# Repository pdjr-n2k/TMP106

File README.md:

# TMP106 - NMEA 2000 temperature sensor module

This project provides a 
[hardware design](./hardware/)
and associated
[firmware](./firmware/)
for an NMEA 2000 six channel temperature sensor module.

There is also a
[user manual](./user/README.md)
for a device built using these two components.

**TMP106** is a specialisation of
[NOP100](https://www.github.com/preeve9534/NOP100).

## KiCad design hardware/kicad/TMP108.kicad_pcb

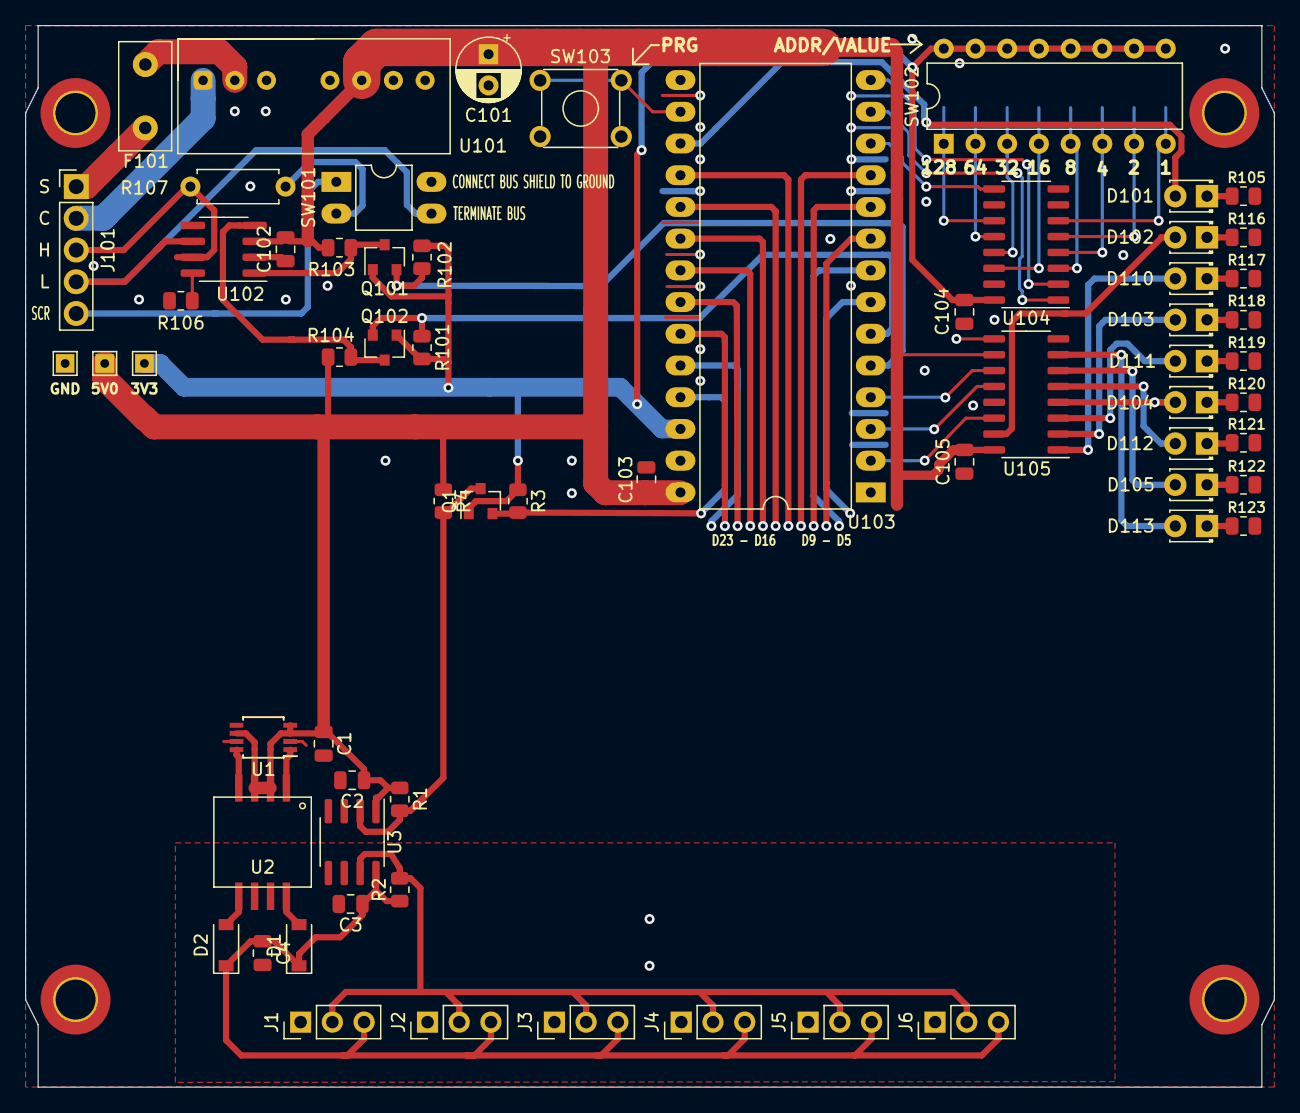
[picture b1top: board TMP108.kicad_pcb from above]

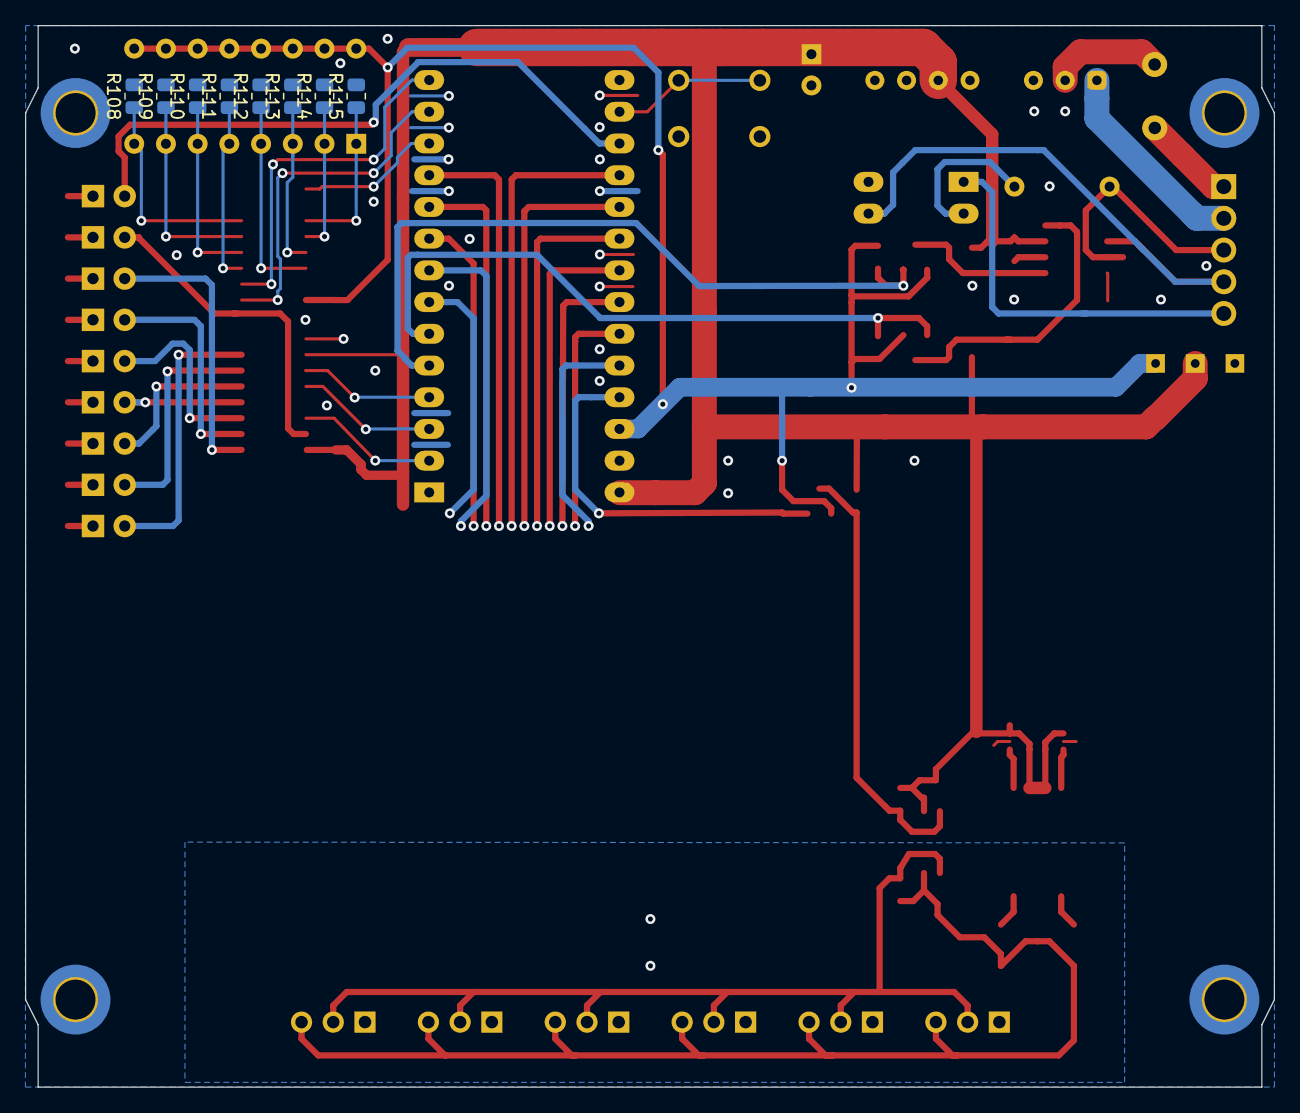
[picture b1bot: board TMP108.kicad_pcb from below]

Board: 2 copper layers, 100.0 x 85.0 mm, 71 parts (8 on the bottom side), 57 nets.

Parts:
C1, C3: 10uF; C_0805_2012Metric
C2, C4: 20nF; C_0805_2012Metric
C101: 100nF; CP_Radial_D5.0mm_P2.50mm
C102, C103, C104, C105: 100nF; C_0805_2012Metric
D1, D2: MBR0520LT; D_SOD-123
D101, D102, D103, D104, D105, D110, D111, D112, D113: LED; LED_D1.8mm_W3.3mm_H2.4mm
F101: 1A; Fuse_Littelfuse_395Series
J1, J2, J3, J4, J5, J6: Screw_Terminal_01x03; PinHeader_1x03_P2.54mm_Vertical
J101: CAN; PinHeader_1x05_P2.54mm_Vertical
Q1, Q101, Q102: BSS138; SOT-23
R1, R2: 1K; R_0805_2012Metric
R3, R4: 10K; R_0805_2012Metric
R101, R102, R103, R104: 10K 0.125W; R_0805_2012Metric
R105, R116, R117, R118, R119, R120, R121, R122, R123: 560R; R_0805_2012Metric
R106, R108, R109, R110, R111, R112, R113, R114, R115: 4K7 0.125W; R_0805_2012Metric
R107: 120R 0.5W; R_Axial_DIN0207_L6.3mm_D2.5mm_P7.62mm_Horizontal
SW101: BUS; DIP-4_W7.62mm_LongPads
SW102: ADDR/VALUE; DIP-16_W7.62mm
SW103: PRG; SW_TH_Tactile_Omron_B3F-10xx
TEST 5V0, TEST 5V0#2: TestPoint_THTPad_1.5x1.5mm_Drill0.7mm
U1: MAX845; TSSOP-8_3x3mm_P0.65mm
U2: TGM-050P3RL; TGM-010P3RL
U3: ISO1540; SOIC-8_3.9x4.9mm_P1.27mm
U101: TMR-2-2411; TMR_2411
U102: MCP2551-I-P; SOIC-8_3.9x4.9mm_P1.27mm
U103: Teensy_4.0; DIP-28_W15.24mm_LongPads
U104: 74HC165; SO-16_3.9x9.9mm_P1.27mm
U105: 74HCT595; SO-16_3.9x9.9mm_P1.27mm

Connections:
+3V3: C104.1, Q1.1, Q101.1, Q102.1, R3.1, R101.2, R102.2, SW102.9, SW102.10, SW102.11, SW102.12, SW102.13, SW102.14, SW102.15, SW102.16, TEST 5V0.1, U103.26, U104.16
+5V: C1.1, C2.1, C101.1, C102.1, C103.1, C105.1, R1.1, R4.1, R103.2, R104.2, TEST 5V0#2.1, U1.3, U1.4, U1.6, U2.2, U2.3, U3.1, U101.6, U102.3, U103.28, U105.10, U105.16
/CAN_RX: Q102.2, R101.1, U103.6
/CAN_TX: Q101.2, R102.1, U103.5
/D23: Q1.2, R3.2, U103.25
/PISO_CP: U103.14, U104.2
/PISO_PL: U103.13, U104.1
/PISO_Q7: U103.12, U104.9
/PRG: SW103.1, SW103.2, U103.16
/SIPO_CLOCK: U103.4, U105.11
/SIPO_DATA: U103.2, U105.14
/SIPO_LATCH: U103.3, U105.12
GND: C1.2, C2.2, C101.2, C102.2, C103.2, C104.2, C105.2, R105.2, R106.1, R108.2, R109.2, R110.2, R111.2, R112.2, R113.2, R114.2, R115.2, R116.2, R117.2, R118.2, R119.2, R120.2, R121.2, R122.2, R123.2, SW101.4, SW103.3, SW103.4, U1.2, U1.7, U3.4, U101.7, U102.2, U103.1, U103.27, U104.8, U104.10, U104.15, U105.8, U105.13
GNDREF: C3.2, C4.2, J1.1, J2.1, J3.1, J4.1, J5.1, J6.1, U2.6, U2.7, U3.5
unnamed: D1.2, U2.8
unnamed: D2.2, U2.5
unnamed: D101.1, R105.1
unnamed: D101.2, U103.17
unnamed: D102.1, R116.1
unnamed: D102.2, U105.15
unnamed: D103.1, R118.1
unnamed: D103.2, U105.2
unnamed: D104.1, R120.1
unnamed: D104.2, U105.4
unnamed: D105.1, R122.1
unnamed: D105.2, U105.6
unnamed: D110.1, R117.1
unnamed: D110.2, U105.1
unnamed: D111.1, R119.1
unnamed: D111.2, U105.3
unnamed: D112.1, R121.1
unnamed: D112.2, U105.5
unnamed: D113.1, R123.1
unnamed: D113.2, U105.7
unnamed: F101.1, J101.1
unnamed: F101.2, U101.2
unnamed: J1.2, J2.2, J3.2, J4.2, J5.2, J6.2, R2.2, U3.7
unnamed: J101.2, U101.1
unnamed: J101.3, R107.1, U102.7
unnamed: J101.4, SW101.3, U102.6
unnamed: J101.5, SW101.1
unnamed: Q1.3, R1.2, R4.2, U3.2
unnamed: Q101.3, R103.1, U102.1
unnamed: Q102.3, R104.1, U102.4
unnamed: R106.2, U102.8
unnamed: R107.2, SW101.2
unnamed: R108.1, SW102.8, U104.6
unnamed: R109.1, SW102.7, U104.5
unnamed: R110.1, SW102.6, U104.4
unnamed: R111.1, SW102.5, U104.3
unnamed: R112.1, SW102.4, U104.14
unnamed: R113.1, SW102.3, U104.13
unnamed: R114.1, SW102.2, U104.12
unnamed: R115.1, SW102.1, U104.11
unnamed: U1.1, U2.1
unnamed: U1.8, U2.4
VDD: C3.1, C4.1, D1.1, D2.1, J1.3, J2.3, J3.3, J4.3, J5.3, J6.3, R2.1, U3.8

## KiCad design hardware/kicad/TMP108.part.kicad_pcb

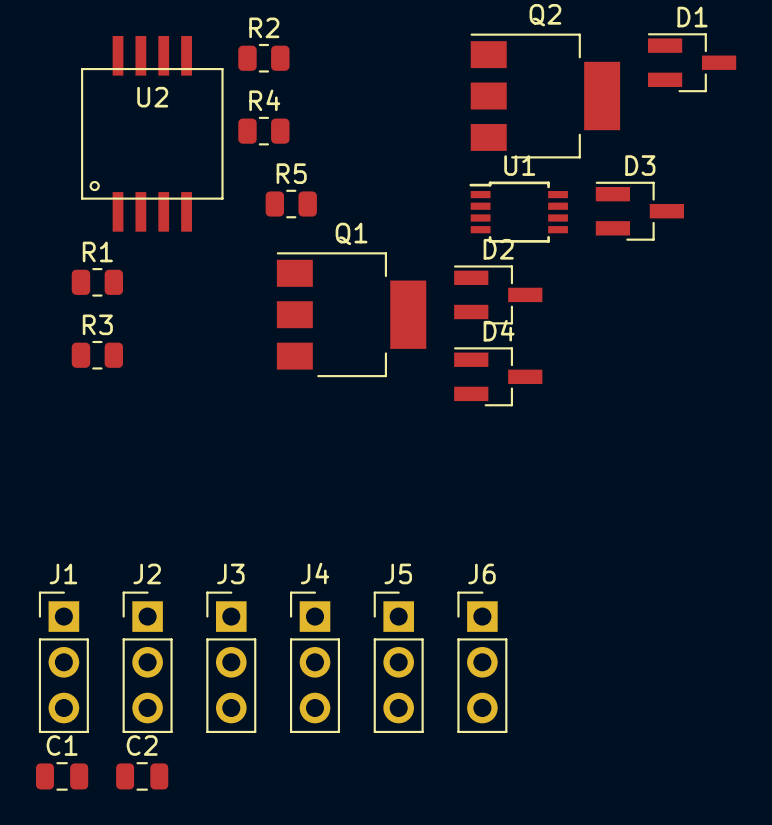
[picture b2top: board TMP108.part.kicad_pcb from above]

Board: 2 copper layers, 21 parts (0 on the bottom side), 14 nets, no tracks yet.

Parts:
C1: 20nF; C_0805_2012Metric
C2: 1nF; C_0805_2012Metric
D1, D2, D3, D4: D_Schottky_Small; SOT-23_Handsoldering
J1, J2, J3, J4, J5, J6: Screw_Terminal_01x03; PinHeader_1x03_P2.54mm_Vertical
Q1, Q2: 2N3904; SOT-223
R1: 2K2; R_0805_2012Metric
R2: 75R; R_0805_2012Metric
R3: 390R; R_0805_2012Metric
R4: 1K; R_0805_2012Metric
R5: 10K; R_0805_2012Metric
U1: MAX845; TSSOP-8_3x3mm_P0.65mm
U2: TGM-010P3RL

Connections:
+5V: R1.2, U1.3, U1.4, U2.2, U2.3
/D23: Q1.3, R1.1
GND: C1.2, Q1.1, R2.1
unnamed: C1.1, Q1.2, R2.2, U1.2, U1.7
unnamed: C2.1, D2.2, D4.2, J1.1, J2.1, J3.1, J4.1, J5.1, J6.1, Q2.3
unnamed: C2.2, D1.1, D3.1, R3.1, R4.1
unnamed: D1.2, D2.1, U2.8
unnamed: D3.2, D4.1, U2.5
unnamed: J1.2, J2.2, J3.2, J4.2, J5.2, J6.2, R4.2
unnamed: J1.3, J2.3, J3.3, J4.3, J5.3, J6.3, R5.2
unnamed: Q2.1, R3.2
unnamed: Q2.2, R5.1
unnamed: U1.1, U2.1
unnamed: U1.8, U2.4

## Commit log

2022-06-06 Initialise repo.
2022-06-06 Add kicad library as submodule.
2022-06-06 Correct SID management
2022-06-06 Adjust PCB silk screen
2022-06-07 Restore to working version.
2022-06-07 Add smoothing capacitor to PSU
    1000uF capacitor across 5V output to manage instability in ADC reference voltage.
2022-06-08 Board tweaks
    To avoid PCB fouling cover clips.
2022-06-08 Add cable tie holes to PCB
2022-06-08 Update TMP108.cpp
    Define constants for ADC behaviour.
2022-06-08 Update TMP108.cpp
    Refactor and tidy up.
2022-06-09 Add transmission queue handling
2022-06-09 Queued transmission.
2022-06-09 Amend debug format
2022-06-10 Add CAN terminator
2022-06-10 Routing
2022-06-10 Reroute PCB
2022-06-10 PCB drill check.
2022-06-10 Add LED for transmit interval
2022-06-11 Route tweak
2022-06-12 stuff
2022-06-12 Board reroute.
2022-06-12 Reformat PCB labels
2022-06-12 PCB parts list, etc.
2022-06-13 Add configuration features
2022-06-13 Typo.
2022-06-13 |README tweaks
2022-06-13 Parts list
2022-06-14 Increase PCB notch size.
2022-06-14 Adjust silk screen
2022-06-14 New PCB image
2022-06-14 Reassign LED GPIO
2022-06-15 README updates.
2022-06-15 PCB tweak.
2022-06-19 Improve user feedback during configuration
2022-06-20 Reroute PCB.
2022-06-23 Twaeks,
2022-06-25 Tweaks
2022-12-28 Tweak
2022-12-31 Isolate temperature sensors
2022-12-31 New layout
2022-12-31 Start the code
2023-01-01 Getting started
2023-01-02 Lots of development
2023-01-02 Coding
2023-01-02 More code
2023-01-03 First compile
2023-01-03 Tidy ups.
2023-01-04 Tidy up
2023-01-04 Voltage shift D23
2023-01-04 Status LEDs.
2023-01-04 Lots of commentary.
2023-01-05 Rename global
2023-01-05 Readme tweaks.
2023-01-06 Refactor
2023-01-09 New module configuration code
2023-01-09 New configuration mechanism
2023-01-13 Documentation.
2023-01-29 Update fp-info-cache
2023-05-05 Revise OneWireAddress
2023-05-05 Move to public library
2023-05-06 Refactor.
